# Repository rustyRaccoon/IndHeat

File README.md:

# IndutiveHeater
 Inductive heater based on an astable MOSFET oscillator and an LC tank

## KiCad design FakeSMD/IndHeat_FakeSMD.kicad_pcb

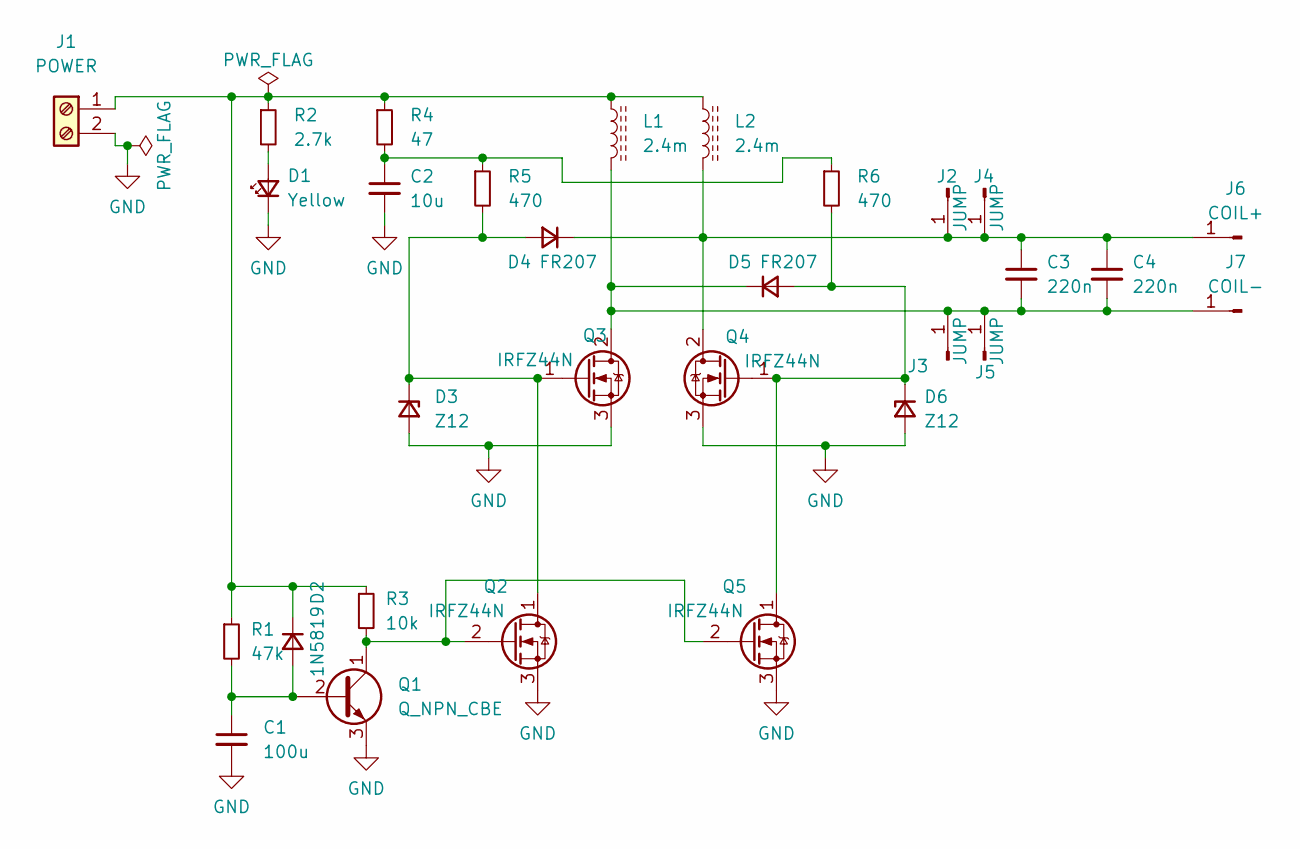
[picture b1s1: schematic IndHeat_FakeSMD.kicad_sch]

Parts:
C1: 100u; C_Radial_D6.3mm_H5.0mm_P2.50mm
C2: 10u; C_Radial_D6.3mm_H5.0mm_P2.50mm
C3, C4: 220n; C_Rect_L18.0mm_W9.0mm_P15.00mm_FKS3_FKP3
D1: Yellow; LED_D5.0mm
D2: 1N5819; D_DO-41_SOD81_P10.16mm_Horizontal
D3, D6: Z12; D_DO-41_SOD81_P7.62mm_Horizontal
D4, D5: FR207; D_DO-15_P12.70mm_Horizontal
J1: POWER; TerminalBlock_RND_205-00012_1x02_P5.00mm_Horizontal
J2, J3: JUMP; PinSocket_1x01_P2.54mm_Vertical
J4, J5: JUMP; JumperHole_2mm
J6: COIL+; JumperHole_2mm
J7: COIL-; JumperHole_2mm
L1, L2: 2.4m; Toroid_35mm
Q1: Q_NPN_CBE; TO-92_Inline
Q2, Q5: IRFZ44N; SOT-23_Handsoldering
Q3, Q4: IRFZ44N; TO-220-3_Vertical
R1: 47k; R_1206_3216Metric_Pad1.30x1.75mm_HandSolder
R2: 2.7k; R_Axial_DIN0207_L6.3mm_D2.5mm_P2.54mm_Vertical
R3: 10k; R_1206_3216Metric_Pad1.30x1.75mm_HandSolder
R4: 47; R_Axial_DIN0207_L6.3mm_D2.5mm_P7.62mm_Horizontal
R5, R6: 470; R_Axial_DIN0207_L6.3mm_D2.5mm_P7.62mm_Horizontal

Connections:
GND: C1.2, C2.2, D1.1 (K), D3.2 (A), D6.2 (A), J1.2, Q1.3 (E), Q2.3 (S), Q3.3 (S), Q4.3 (S), Q5.3 (S)
unnamed: C1.1, D2.2 (A), Q1.2 (B), R1.2
unnamed: C2.1, R4.2, R5.1, R6.1
unnamed: C3.1, C4.1, D4.1 (K), J2.1, J4.1, J6.1, L2.2, Q4.2 (D)
unnamed: C3.2, C4.2, D5.1 (K), J3.1, J5.1, J7.1, L1.2, Q3.2 (D)
unnamed: D1.2 (A), R2.2
unnamed: D2.1 (K), J1.1, L1.1, L2.1, R1.1, R2.1, R3.1, R4.1
unnamed: D3.1 (K), D4.2 (A), Q2.1 (D), Q3.1 (G), R5.2
unnamed: D5.2 (A), D6.1 (K), Q4.1 (G), Q5.1 (D), R6.2
unnamed: Q1.1 (C), Q2.2 (G), Q5.2 (G), R3.2

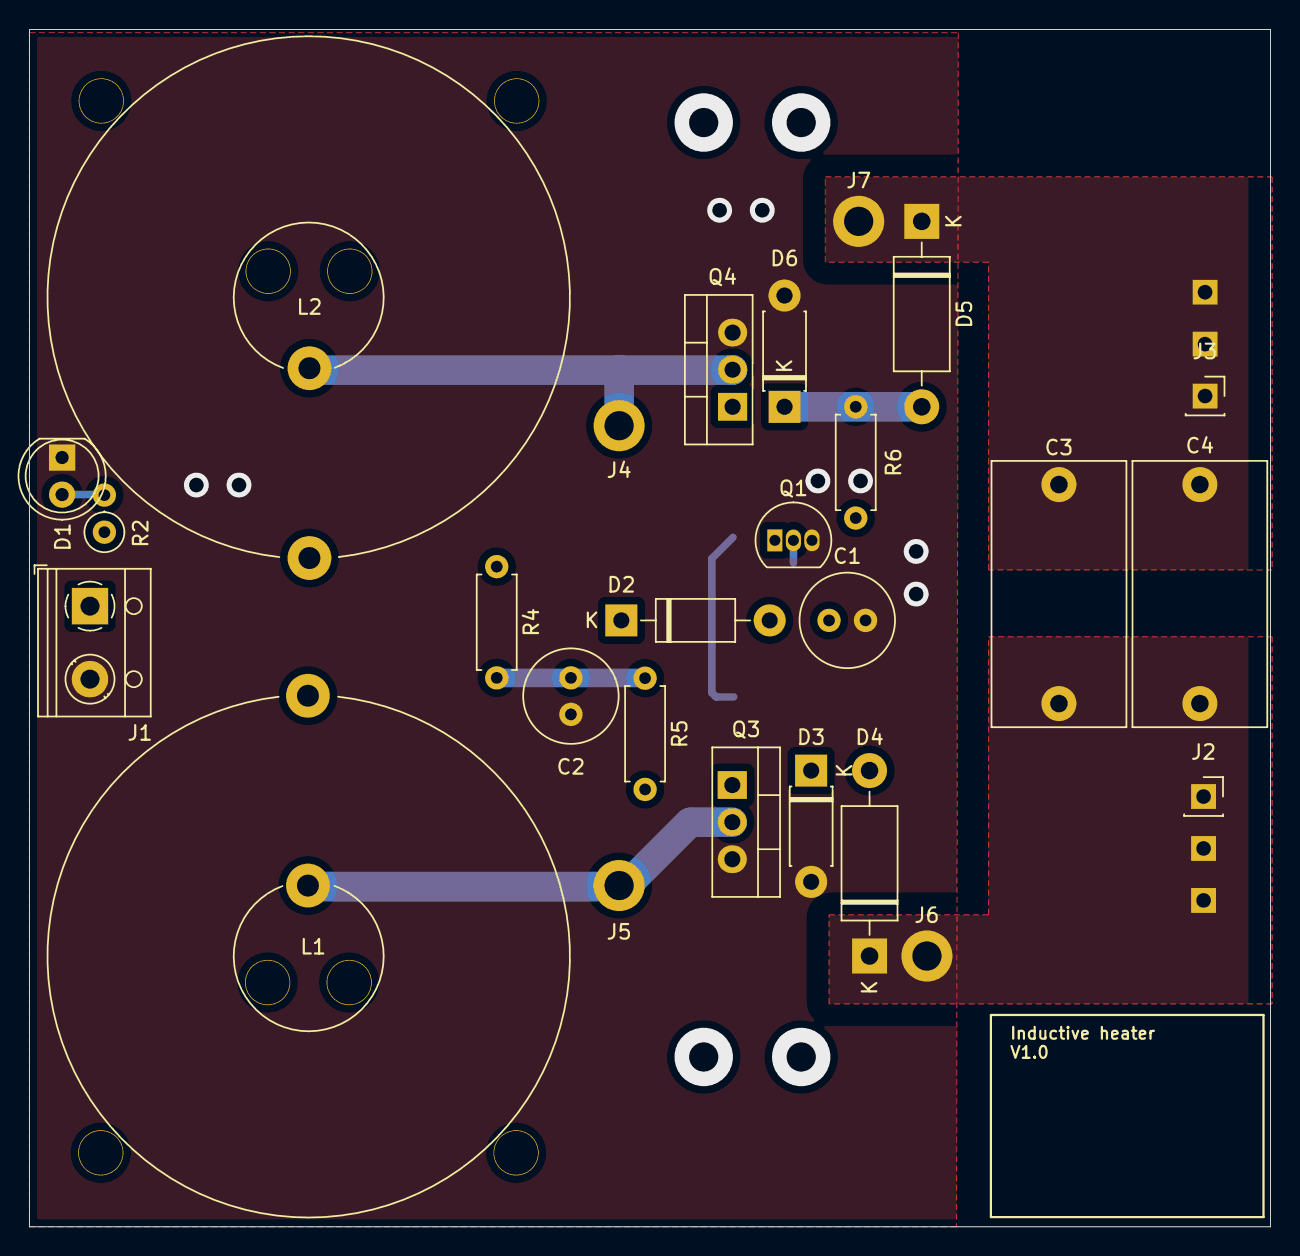
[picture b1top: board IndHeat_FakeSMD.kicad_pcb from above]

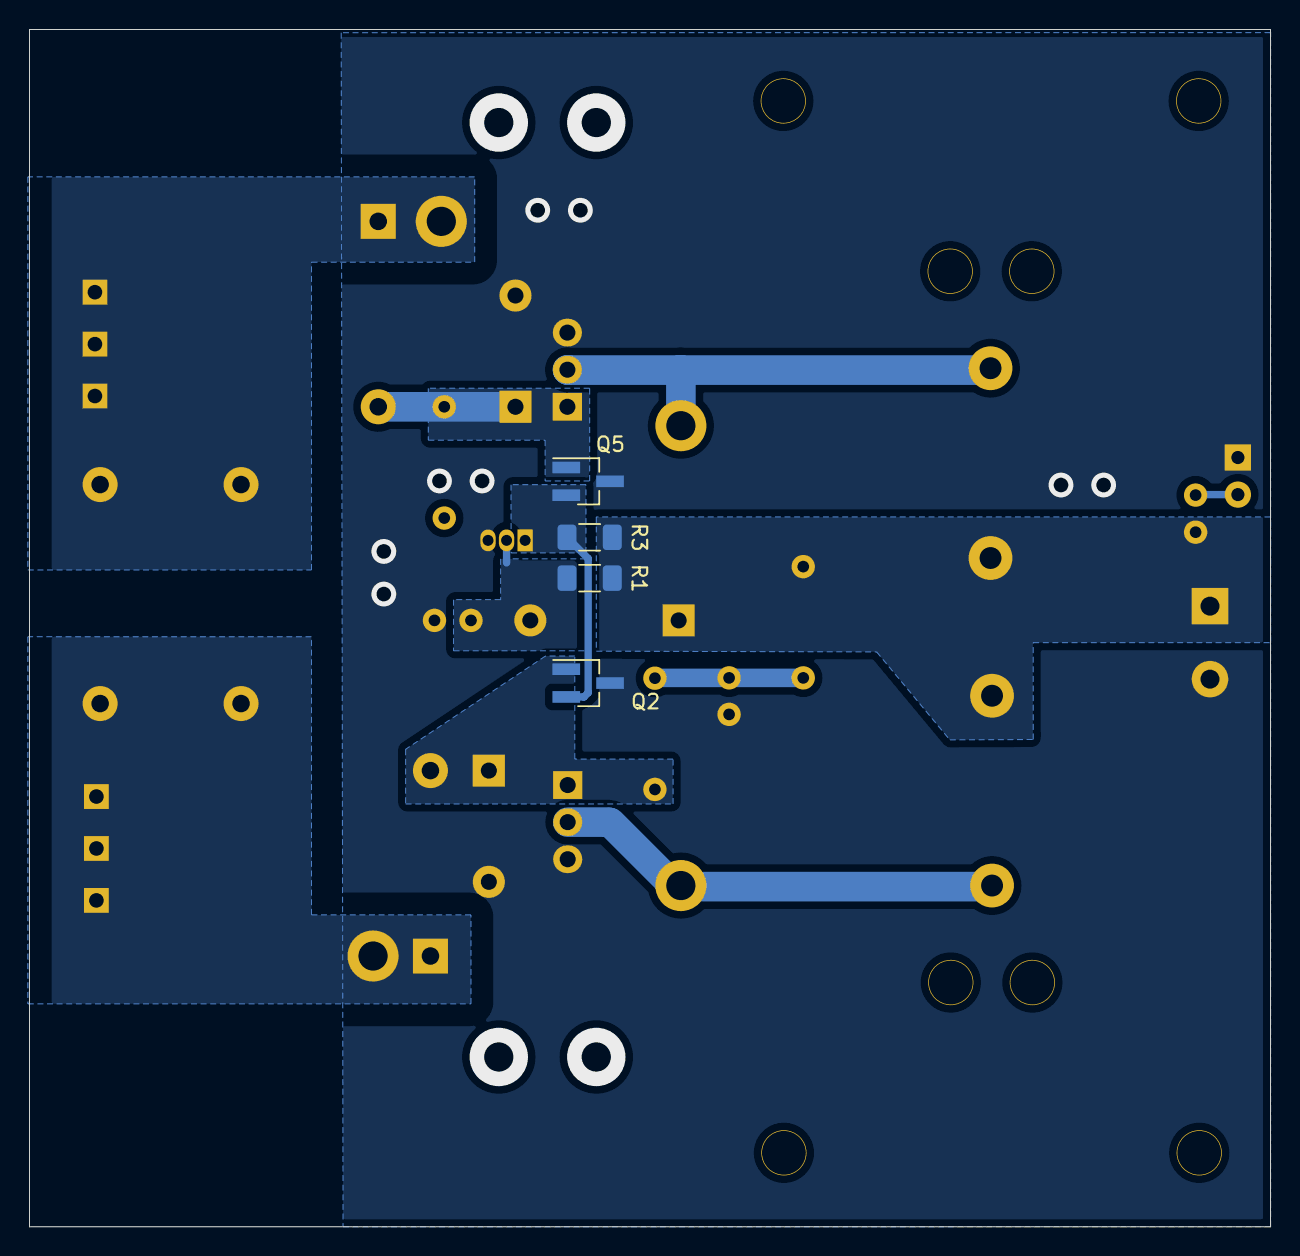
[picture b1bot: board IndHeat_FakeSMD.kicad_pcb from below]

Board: 2 copper layers, 85.0 x 82.0 mm, 30 parts (4 on the bottom side), 10 nets.

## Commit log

2023-03-25 Deleted backups
